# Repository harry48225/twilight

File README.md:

# ```twlight```

An automated roller blind opener. Using an esp32 runing micropython.

## ```twilight.local```
The esp32 serves a svelte webapp on ``` twilight.local```. See ```firmware/webapp```

## ```hardware```
A NEMA 17 stepper motor is used to move the blinds. It's connected to a 3d-printed gearbox ```cad/``` providing an ~1:5 reduction. It's driven by a DRV8825 stepper motor driver.

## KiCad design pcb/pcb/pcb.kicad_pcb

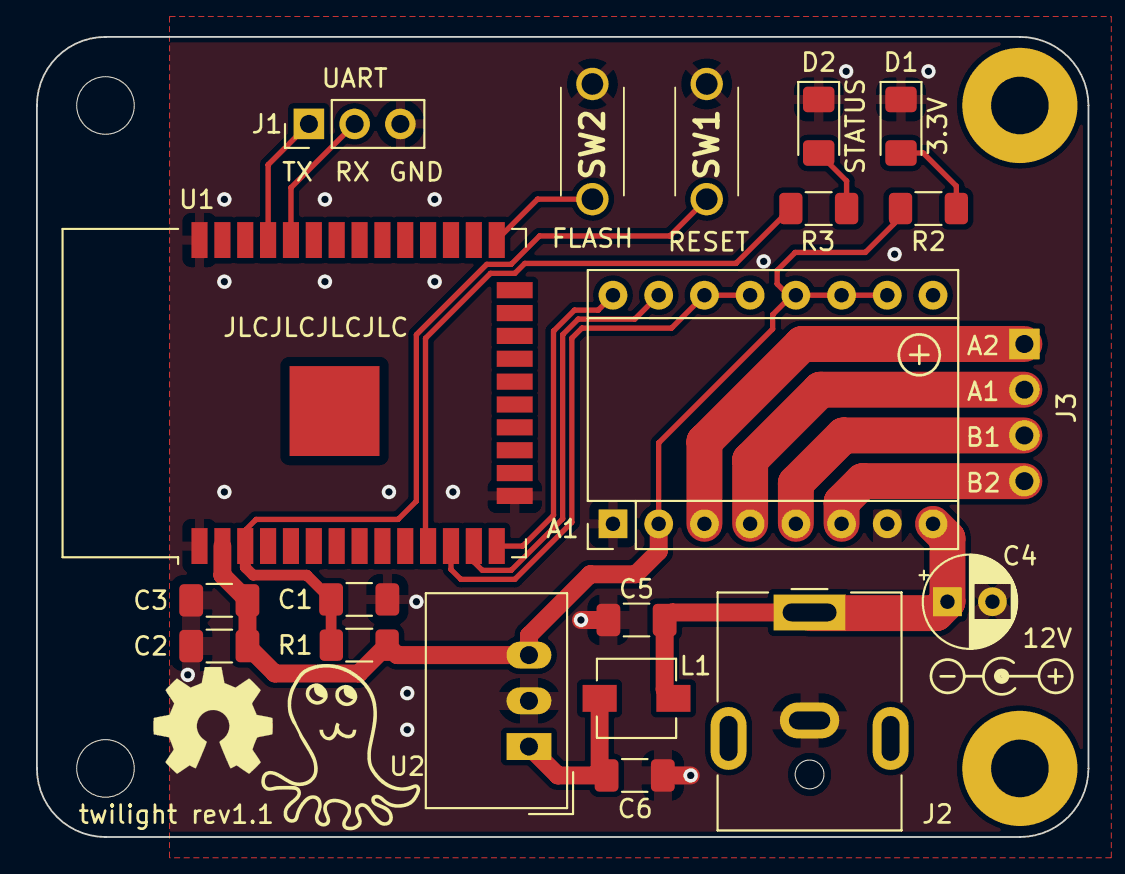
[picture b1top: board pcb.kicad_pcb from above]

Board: 2 copper layers, 58.4 x 44.4 mm, 24 parts (0 on the bottom side), 18 nets.

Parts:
A1: Breakout_DRV8825; Pololu_Breakout-16_15.2x20.3mm
C1, C3: 0.1uF; C_1206_3216Metric_Pad1.33x1.80mm_HandSolder
C2, C5, C6: 10uF; C_1206_3216Metric_Pad1.33x1.80mm_HandSolder
C4: 100uF; CP_Radial_D5.0mm_P2.50mm
D1: LED RED; LED_1206_3216Metric_Pad1.42x1.75mm_HandSolder
D2: LED GREEN; LED_1206_3216Metric_Pad1.42x1.75mm_HandSolder
H1, H3: MountingHole; MountingHole_3.2mm_M3
H2, H4: MountingHole; MountingHole_3.2mm_M3_Pad
J1: UART; PinHeader_1x03_P2.54mm_Vertical
J2: Barrel_Jack; BarrelJack_CUI_PJ-063AH_Horizontal
J3: Stepper; PinHeader_1x04_P2.54mm_Horizontal
L1: 5.6uH; L_TracoPower_TCK-141
R1: 10k; R_1206_3216Metric_Pad1.30x1.75mm_HandSolder
R2, R3: 680; R_1206_3216Metric_Pad1.30x1.75mm_HandSolder
SW1: RESET; PTS636SK43LFS
SW2: FLASH; PTS636SK43LFS
U1: ESP32-WROOM-32
U2: TSR_1-2433; Converter_DCDC_TRACO_TSR-1_THT

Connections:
+3V3: A1.2 (~FLT), A1.10 (M0), A1.11 (M1), A1.12 (M2), C2.1, C3.1, R1.1, R2.1, U1.2 (VDD), U2.3 (Vout)
+12V: A1.8 (VMOT), C4.1, C5.1, J2.1, L1.1
/A1: A1.4 (A1), J3.2
/A2: A1.3 (A2), J3.1
/B1: A1.5 (B1), J3.3
/B2: A1.6 (B2), J3.4
/DIR: A1.16 (DIR), U1.14 (IO12)
/EN: C1.1, R1.2, SW1.1, U1.3 (EN)
/IO0: SW2.1, U1.25 (IO0)
/RX: J1.2, U1.34 (RXD0/IO3)
/SLP: A1.13 (~RST), A1.14 (~SLP), U1.12 (IO27)
/STEP: A1.15 (STEP), U1.13 (IO14)
/TX: J1.1, U1.35 (TXD0/IO1)
GND: A1.1 (GND), A1.7 (GND), C1.2, C2.2, C3.2, C4.2, C5.2, C6.2, D1.1 (K), D2.1 (K), J1.3, J2.2, SW1.2, SW2.2, U1.1 (GND), U1.15 (GND), U1.38 (GND), U1.39 (GND), U2.2 (GND)
unnamed: C6.1, L1.2, U2.1 (Vin)
unnamed: D1.2 (A), R2.2
unnamed: D2.2 (A), R3.2
unnamed: R3.1, U1.11 (IO26)

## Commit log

2021-12-23 basic sprocket
2021-12-26 Tweak large gear and create small gear
2021-12-26 Create wall plate
2021-12-26 update git ignore
2021-12-27 Updatedwall plate to include motor and basic sketch
2021-12-28 resize small gear
2021-12-28 increase gear size
2021-12-29 add x stepper slots, delete shaft, add captive nut
2021-12-29 add fillet
2021-12-29 Increase gear distance
2021-12-29 Make make for large gear
2021-12-29 increase shaft diameter
2021-12-30 Tweak sizes
2021-12-30 Inital draft
2021-12-31 Add captive fixing nut
2021-12-31 Add captive nut
2021-12-31 Remove old parts
2022-01-01 Add firmware skeleton
2022-01-01 Add credentials file
2022-01-01 build upy 1.17 against esp-if v4.4 try to fix mdns
2022-01-01 implement basic network connection
2022-01-01 Add microdot webserver
2022-01-01 Move to async webserver
2022-01-01 Add basic on and off controls
2022-01-02 Increase cpu frequency
2022-01-02 Add webapp scaffolding
2022-01-02 Convert to typescript
2022-01-02 Strip unneeded boilerplate
2022-01-02 Setup build scripts
2022-01-02 Serve svelte app
2022-01-02 Add lower and raise buttons
2022-01-02 Add scss
2022-01-02 Add basic sun position table
2022-01-02 Switch to mono font
2022-01-02 Add basic scheduler
2022-01-02 Shorten scheduler text
2022-01-02 Add ntp time
2022-01-03 Add suncalc
2022-01-03 Add skeleton motor controller class
2022-01-03 fix ntp timeout error
2022-01-03 Add open and close methods to motor class
2022-01-03 Add lower and raise endpoints
2022-01-03 Make raise and lower buttons functional
2022-01-03 Add isometric blind
2022-01-03 Add windowsill
2022-01-03 Add animation to height changes
2022-01-04 Convert height to normalised
2022-01-04 Fetch height from api
2022-01-04 Add sun times fetching from backend
2022-01-04 double motor speed
2022-01-04 Speed increase
2022-01-06 Add power and motor driver
2022-01-06 Add esp32
2022-01-06 basic pcb layout
2022-01-06 Route pcb
2022-01-06 Add silkscreen
2022-01-07 Update micropython firmware to remove wifi sleep
2022-01-07 motor refactor
2022-01-07 Make motor loop blocking, vastly increasing speed
2022-01-07 Make ui update when blind action is complete
2022-01-07 Tweak motor speed
2022-01-07 Switch to 1/32 step mode
2022-01-10 Add screenshot
2022-01-10 Add gears photo
2022-01-10 Move images
2022-01-23 add reset and boot buttons
2022-01-23 route traces
2022-01-23 Add power led
2022-01-23 add copper pours
2022-01-23 tweaks from reddit wiki
2022-01-27 add activity led and general tidy
2022-01-30 general tweaks
2022-01-30 tidy schematic
2022-01-30 Reroute pcb
2022-02-01 third reddit revision
2022-02-03 change minimum via size and tweak traces
2022-02-04 fix mounting hole footprint in schematic
2022-02-04 add more silkscreen
2022-02-11 small layout tweaks
2022-02-11 add octopus icon
2022-02-11 generate gerbers and 3d model
2022-03-04 change resistor values to more standard
2022-03-27 Change pin assignments to match PCB
2022-03-27 Update pins to match pcb
2022-03-27 Add watchdog timer
2022-03-27 Feed watchdog during motor moves
2022-03-27 Update pcb to fix bugs
2022-03-27 Optimise routing
2022-03-28 Add home assistant configuration
2022-03-28 pcb wall mount
2022-12-18 basic gears
2022-12-18 position gears
2022-12-18 add remaining planetary gears
2022-12-18 add bearings
2022-12-18 initial carrier
2022-12-18 mounting points and stepper
2022-12-18 add mounting arm
2022-12-18 add more braxkets
2022-12-18 change wall plate mounting
2022-12-18 rotate wall brackets
2022-12-18 adding wall mounting to wall plate
2022-12-18 add motor mounts
2022-12-18 add nuts for motor mount
2022-12-18 create sprocket
2022-12-18 add screws to planet carrier
2022-12-18 add mounting for sun gear
2022-12-19 add more clearance
2022-12-19 add front reatainer
2022-12-19 fix wall brackets
2022-12-19 add retainers
2022-12-20 adjust wall plate
2022-12-21 sprocket tweaks
2022-12-27 small tweaks
2023-01-01 Bevel gears
2023-01-01 refine bevel gears
2023-01-01 basic second stage
